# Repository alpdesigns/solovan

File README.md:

# Solovan
Solovan is a 15x3 ortholinear mechanical keyboard.

## Build Guides / ビルドガイド

- [Rev.A](./buildguide/rev_a)

## Firmware / ファームウェア

This keyboard uses the QMK firmware.

- https://github.com/alpdesigns/qmk_firmware
## PCB Data / 基板データ
### PCB Data License
- Licensed under a [Creative Commons Attribution-NonCommercial-ShareAlike 4.0 International License](http://creativecommons.org/licenses/by-nc-sa/4.0/) (CC BY-NC-SA 4.0) otherwise noted. 
- For footprints see https://github.com/kymok/kicad-libs.

### data

- [Rev.A](./pcb/rev_a) (MCU: ATMEGA32u4)

## Bottom Plate Data / 底面プレートデータ

### Bottom Plate Data License

(C) ALP Designs 2021 All Rights Reserved.
- The data are provided for convenience of making accessories such as jigs or fixtures.
- 治具や固定金物などのアクセサリ制作に便利なよう，穴位置の図面を公開しています．

### data

- [Rev.A](./drawings/)

## Discord

- https://discord.gg/nhzya4kw

## Acknowledgements / 謝辞

I am grateful to [しろし](https://twitter.com/shirofox) for discussing the spec and giving me useful feedbacks through prototyping phase. Also [オタヒーのサメ](https://twitter.com/otahinosame) for naming this keyboard. [QMK Firmware](https://qmk.fm), [KiCad](https://www.kicad.org), [REMAP](https://remap-keys.app) were the indispensable OSS projects that this keyboard relies on. I would like to thank [SMKiJ members](https://self-made-keyboards-in-japan.github.io) for generously sharing their experience and knowledge.

開発にあたり，[しろし](https://twiter.com/shirofox)さんに仕様の議論とプロトタイプの試用にご協力いただきました．[オタヒーのサメ](https://twitter.com/otahinosame)さんにはキーボードを命名していただきました．また，[QMK Firmware](https://qmk.fm), [KiCad](https://www.kicad.org), [REMAP](https://remap-keys.app) は欠くことのできない重要な OSS プロジェクトでした．経験と知識を日々共有してくださる [SMKiJ](https://self-made-keyboards-in-japan.github.io) の皆様には日々お世話になっています．この場を借りて感謝申し上げます．

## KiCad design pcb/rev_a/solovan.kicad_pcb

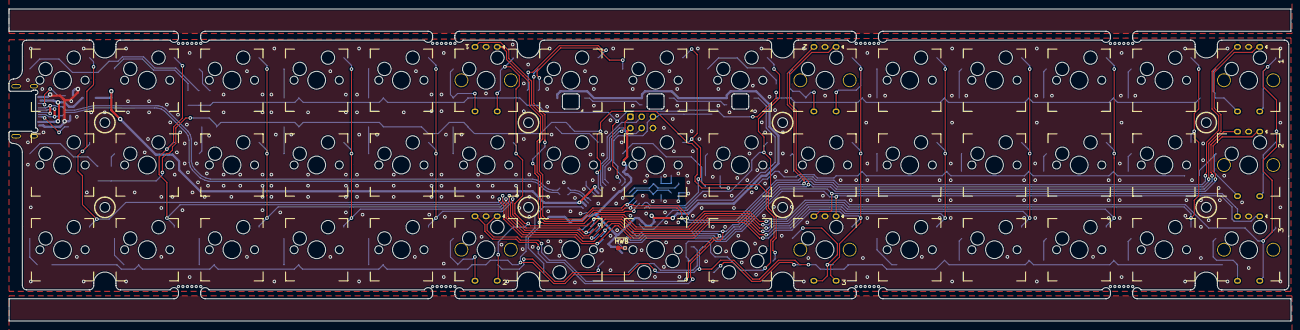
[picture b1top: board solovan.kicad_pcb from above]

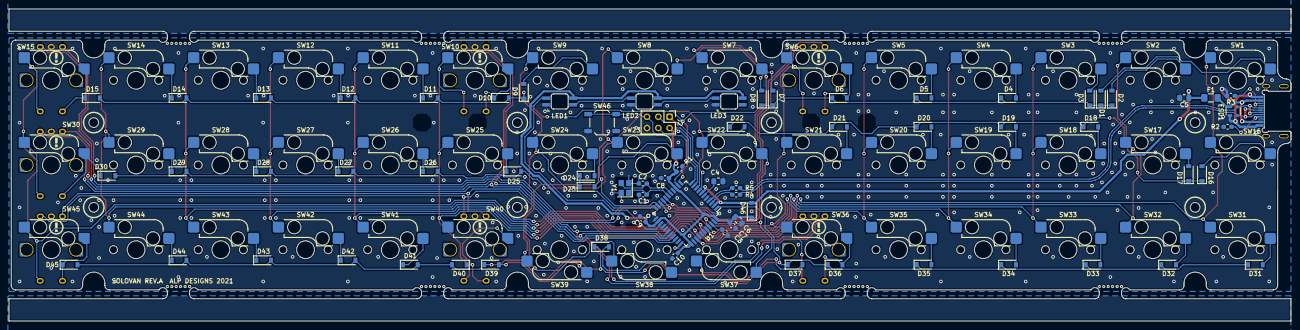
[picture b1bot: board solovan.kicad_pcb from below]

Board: 2 copper layers, 288.3 x 70.1 mm, 133 parts (71 on the bottom side), 85 nets.

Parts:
C1: 10p; C_0603_1608Metric_Pad1.08x0.95mm_HandSolder
C2: 10p; C_0603_1608Metric_Pad1.05x0.95mm_HandSolder
C3, C7, C8, C9, C10: 0.1u; C_0603_1608Metric_Pad1.05x0.95mm_HandSolder
C4, C5, C6: 1u; C_0805_2012Metric_Pad1.15x1.40mm_HandSolder
D1, D2, D3, D4, D5, D6, D7, D8, D9, D10, D11, D12, D13, D14, D15, D16, D17, D18, D19, D20, D21, D22, D23, D24, D25, D26, D27, D28, D29, D30, D31, D32, D33, D34, D35, D36, D37, D38, D39, D40, D41, D42, D43, D44, D45: 1N4148W; D_SOD-123
D46: 1N5819HW-7-F; D_SOD-123
ESD1: PRTR5V0U2X; SOT-143B
F1: 1206L050YR; Fuse_1206_3216Metric_Pad1.42x1.75mm_HandSolder
H1, H2, H3, H4, H5, H6, H7, H8: MountingHole; MountingHole_M2
H11, H12, H13, H14, H15, H16, H17, H18: MountingHole; Breakaway
J1: USB_C_Receptacle_USB2.0; HRO_TYPE_C_31_M_13
J2: ICSP; ICSP_ConnThrough
LED1, LED2, LED3: YS-SK6812MINI-E
NT1: Net-Tie_2; NetTie
R1: 10k; R_0603_1608Metric_Pad1.05x0.95mm_HandSolder
R2, R3: 5.1k; R_0603_1608Metric_Pad1.05x0.95mm_HandSolder
R4, R5: 22; R_0603_1608Metric_Pad1.05x0.95mm_HandSolder
SW1, SW2, SW3, SW4, SW5, SW7, SW8, SW9, SW11, SW12, SW13, SW14, SW16, SW17, SW18, SW19, SW20, SW21, SW22, SW23, SW24, SW25, SW26, SW27, SW28, SW29, SW31, SW32, SW33, SW34, SW35, SW37, SW38, SW39, SW41, SW42, SW43, SW44: Kailh MX Socket; SW_Cherry_MX_1.00u_Kailh
SW6, SW10, SW15, SW30, SW36, SW40, SW45: Rotary_Encoder_Switch_MP; SW_Cherry_MX_1.00u_Kailh_EC12
SW46: TS-1187A-B-A-B; SW_SPST_TL3342
U1: ATmega32U4-AU; TQFP-44_10x10mm_P0.8mm
Y1: X322516MLB4SI; Crystal_SMD_3225-4Pin_3.2x2.5mm

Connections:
/Col01: SW1.2, SW10.S1, SW16.2, SW25.2, SW31.2, SW40.S1, U1.36
/Col02: SW2.2, SW11.2, SW17.2, SW26.2, SW32.2, SW41.2, U1.37
/Col03: SW3.2, SW12.2, SW18.2, SW27.2, SW33.2, SW42.2, U1.38
/Col04: SW4.2, SW13.2, SW19.2, SW28.2, SW34.2, SW43.2, U1.39
/Col05: SW5.2, SW14.2, SW20.2, SW29.2, SW35.2, SW44.2, U1.40
/Col06: SW6.S1, SW15.S1, SW21.2, SW30.S1, SW36.S1, SW45.S1, U1.41
/Col07: SW7.1, SW22.1, SW37.2, U1.20
/Col08: SW8.2, SW23.2, SW38.1, U1.21
/Col09: SW9.2, SW24.2, SW39.1, U1.22
/D+: R5.1, U1.4
/D-: R4.1, U1.3
/MISO: J2.1, U1.11
/MOSI: J2.4, U1.10
/RE1A: SW6.A, SW15.A, U1.19
/RE1B: SW6.B, SW15.B, U1.18
/RE2A: SW10.A, SW30.A, SW36.A, U1.29
/RE2B: SW10.B, SW30.B, SW36.B, U1.28
/RE3A: SW40.A, SW45.A, U1.31
/RE3B: SW40.B, SW45.B, U1.30
/RGBLED: LED1.4, U1.25
/Row1: D1.1, D2.1, D3.1, D4.1, D5.1, D6.1, D7.1, D8.1, D9.1, D10.2, D11.2, D12.2, D13.2, D14.2, D15.2, U1.12
/Row2: D16.1, D17.1, D18.1, D19.1, D20.1, D21.1, D22.1, D23.1, D24.1, D25.2, D26.2, D27.2, D28.2, D29.2, D30.2, U1.8
/Row3: D31.1, D32.1, D33.1, D34.1, D35.1, D36.1, D37.1, D38.1, D39.1, D40.2, D41.2, D42.2, D43.2, D44.2, D45.2, U1.1
/SCK: J2.3, U1.9
/USBC_D1+: ESD1.3, J1.A6, J1.B6, R5.2
/USBC_D1-: ESD1.2, J1.A7, J1.B7, R4.2
/~RESET: J2.5, R1.2, SW46.1, U1.13
GND: C1.2, C2.2, C3.1, C4.1, C5.2, C6.2, C7.2, C8.2, C9.2, C10.2, ESD1.1, J1.A1, J1.A12, J1.B1, J1.B12, J1.S1, J2.6, LED1.3, LED2.3, LED3.3, NT1.2, R2.1, R3.1, SW6.C, SW10.C, SW15.C, SW30.C, SW36.C, SW40.C, SW45.C, SW46.2, U1.5, U1.15, U1.23, U1.35, U1.43, Y1.2, Y1.4
unnamed: C1.1, U1.17, Y1.1
unnamed: C2.1, U1.16, Y1.3
unnamed: C3.2, U1.42
unnamed: C4.2, U1.6
unnamed: D1.2, SW1.1
unnamed: D2.2, SW2.1
unnamed: D3.2, SW3.1
unnamed: D4.2, SW4.1
unnamed: D5.2, SW5.1
unnamed: D6.2, SW6.S2
unnamed: D7.2, SW7.2
unnamed: D8.2, SW8.1
unnamed: D9.2, SW9.1
unnamed: D10.1, SW10.S2
unnamed: D11.1, SW11.1
unnamed: D12.1, SW12.1
unnamed: D13.1, SW13.1
unnamed: D14.1, SW14.1
unnamed: D15.1, SW15.S2
unnamed: D16.2, SW16.1
unnamed: D17.2, SW17.1
unnamed: D18.2, SW18.1
unnamed: D19.2, SW19.1
unnamed: D20.2, SW20.1
unnamed: D21.2, SW21.1
unnamed: D22.2, SW22.2
unnamed: D23.2, SW23.1
unnamed: D24.2, SW24.1
unnamed: D25.1, SW25.1
unnamed: D26.1, SW26.1
unnamed: D27.1, SW27.1
unnamed: D28.1, SW28.1
unnamed: D29.1, SW29.1
unnamed: D30.1, SW30.S2
unnamed: D31.2, SW31.1
unnamed: D32.2, SW32.1
unnamed: D33.2, SW33.1
unnamed: D34.2, SW34.1
unnamed: D35.2, SW35.1
unnamed: D36.2, SW36.S2
unnamed: D37.2, SW37.1
unnamed: D38.2, SW38.2
unnamed: D39.2, SW39.2
unnamed: D40.1, SW40.S2
unnamed: D41.1, SW41.1
unnamed: D42.1, SW42.1
unnamed: D43.1, SW43.1
unnamed: D44.1, SW44.1
unnamed: D45.1, SW45.S2
unnamed: J1.A5, R2.2
unnamed: J1.B5, R3.2
unnamed: LED1.2, LED2.4
unnamed: LED2.2, LED3.4
unnamed: NT1.1, U1.33
UVCC-L: C5.1, D46.2, F1.1, U1.2, U1.7
VBUS-L: ESD1.4, F1.2, J1.A4, J1.A9, J1.B4, J1.B9
VCC-L: C6.1, C7.1, C8.1, C9.1, C10.1, D46.1, J2.2, LED1.1, LED2.1, LED3.1, R1.1, U1.14, U1.24, U1.34, U1.44

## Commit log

2021-12-12 Add PCB data
2021-12-14 fix broken link
2021-12-27 Add hole PDF data
2021-12-28 update drawing files
2022-01-05 update build guide
2022-01-05 update changelog
2022-07-18 Add LED behaviour to the build guide
